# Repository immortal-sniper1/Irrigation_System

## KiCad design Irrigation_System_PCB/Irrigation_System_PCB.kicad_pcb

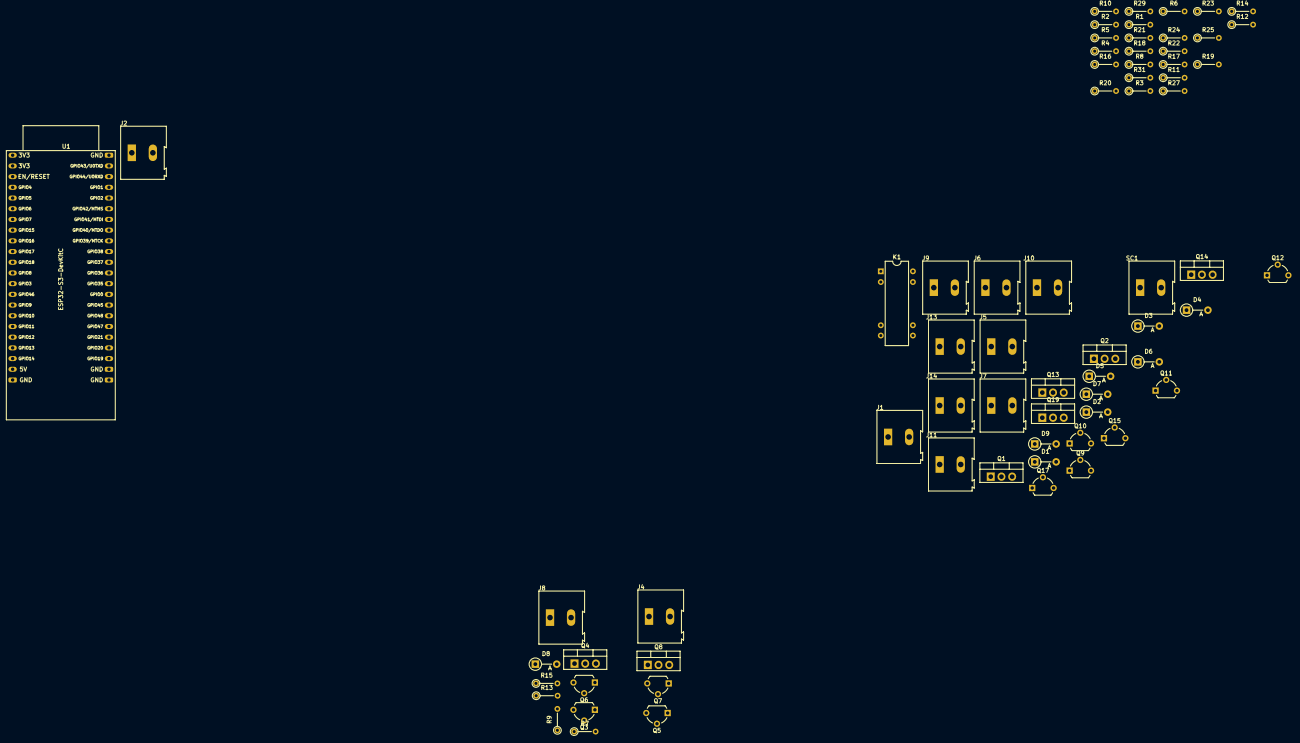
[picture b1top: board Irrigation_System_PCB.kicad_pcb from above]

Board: 2 copper layers, 69 parts (0 on the bottom side), 36 nets, no tracks yet.

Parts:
D1, D2, D3, D4, D5, D6, D7, D8, D9: D_Small; D_A-405_P5.08mm_Vertical_AnodeUp
J1: 12V extern; TerminalBlock_Altech_AK300-2_P5.00mm
J2: baterie; TerminalBlock_Altech_AK300-2_P5.00mm
J4: Solenoid2; TerminalBlock_Altech_AK300-2_P5.00mm
J5: Solenoid3; TerminalBlock_Altech_AK300-2_P5.00mm
J6: adcon_input_wire; TerminalBlock_Altech_AK300-2_P5.00mm
J7: Solenoid4; TerminalBlock_Altech_AK300-2_P5.00mm
J8: Solenoid1; TerminalBlock_Altech_AK300-2_P5.00mm
J9: 12V_in; TerminalBlock_Altech_AK300-2_P5.00mm
J10: 13.5-14V*_out; TerminalBlock_Altech_AK300-2_P5.00mm
J11: Solenoid5*; TerminalBlock_Altech_AK300-2_P5.00mm
J13: 12V*_in; TerminalBlock_Altech_AK300-2_P5.00mm
J14: 5v_out; TerminalBlock_Altech_AK300-2_P5.00mm
K1: DIPxx-1Cxx-51x; Relay_StandexMeder_DIP_LowProfile
Q1, Q2, Q4, Q8, Q13, Q14, Q19: IRF3205; TO-220-3_Vertical
Q3, Q5, Q6, Q7, Q9, Q10, Q11, Q12, Q15, Q17: Q_NMOS_SGD; TO-92L_Wide
R1: 50k; R_Axial_DIN0204_L3.6mm_D1.6mm_P5.08mm_Vertical
R2, R3, R4, R6, R7, R8, R11, R13, R14, R15, R16, R17, R18, R21, R22, R23, R24, R25, R29, R31: 10k; R_Axial_DIN0204_L3.6mm_D1.6mm_P5.08mm_Vertical
R5: 5k; R_Axial_DIN0204_L3.6mm_D1.6mm_P5.08mm_Vertical
R9, R10, R19, R20, R27: DNP; R_Axial_DIN0204_L3.6mm_D1.6mm_P5.08mm_Vertical
R12: 120; R_Axial_DIN0204_L3.6mm_D1.6mm_P5.08mm_Vertical
SC1: Solar_Cells; TerminalBlock_Altech_AK300-2_P5.00mm
U1: ESP32-S3-DevKitC

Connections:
+3V3: R5.1, R13.1, R14.1, R21.1, R22.1, R29.1, U1.1 (3V3), U1.2 (3V3)
+5V: J14.1, U1.21 (5V)
+12V: D1.1 (K), D2.1 (K), D3.1 (K), D4.1 (K), D7.1 (K), D8.1 (K), D9.1 (K), J4.1, J5.1, J7.1, J8.1, J11.1, J13.1, R1.1, R15.1, R16.1, R23.1, R24.1, R31.1
/ADC1: R1.2, R2.1, U1.18 (GPIO12/ADC2_CH1)
GND: D2.2 (A), D6.1 (K), J2.2, J6.2, J9.1, J10.1, J13.2, J14.2, K1.2, Q1.3 (S), Q2.3 (S), Q3.1 (S), Q4.3 (S), Q5.1 (S), Q6.1 (S), Q7.1 (S), Q8.3 (S), Q9.1 (S), Q10.1 (S), Q11.1 (S), Q12.1 (S), Q13.3 (S), Q14.3 (S), Q15.1 (S), Q17.1 (S), Q19.3 (S), R2.2, R6.2, R7.2, R8.2, R11.1, R17.2, R18.2, R25.2, U1.22 (GND), U1.23 (GND), U1.24 (GND), U1.44 (GND)
unnamed: J9.2, K1.7, K1.8
unnamed: J1.2, K1.6, K1.14, R3.1
unnamed: Q1.1 (G), R3.2
unnamed: K1.1, R4.1, SC1.1 (+)
unnamed: Q2.1 (G), R4.2
unnamed: D5.1 (K), D6.2 (A)
unnamed: D5.2 (A), R12.2
unnamed: D1.2 (A), J10.2
unnamed: D3.2 (A), J4.2, Q8.2 (D)
unnamed: D4.2 (A), J5.2, Q13.2 (D)
unnamed: D7.2 (A), J7.2, Q14.2 (D)
unnamed: D8.2 (A), J8.2, Q4.2 (D)
unnamed: D9.2 (A), J11.2, Q19.2 (D)
unnamed: J1.1, Q1.2 (D)
unnamed: Q2.2 (D), SC1.2 (-)
unnamed: Q3.3 (D), Q6.2 (G), R9.2, R13.2
unnamed: Q4.1 (G), Q6.3 (D), R15.2
unnamed: Q5.3 (D), Q7.2 (G), R10.2, R14.2
unnamed: Q7.3 (D), Q8.1 (G), R16.2
unnamed: Q10.3 (D), Q12.2 (G), R20.2, R22.2
unnamed: Q9.3 (D), Q11.2 (G), R19.2, R21.2
unnamed: Q11.3 (D), Q13.1 (G), R23.2
unnamed: Q12.3 (D), Q14.1 (G), R24.2
unnamed: Q15.3 (D), Q17.2 (G), R27.2, R29.2
unnamed: Q17.3 (D), Q19.1 (G), R31.2
unnamed: R5.2, R6.1
unnamed: R11.2, R12.1
VALVE1: Q3.2 (G), R7.1, R9.1
VALVE3: Q9.2 (G), R17.1, R19.1
VALVE4: Q5.2 (G), Q10.2 (G), R8.1, R10.1, R18.1, R20.1
VALVE5: Q15.2 (G), R25.1, R27.1
